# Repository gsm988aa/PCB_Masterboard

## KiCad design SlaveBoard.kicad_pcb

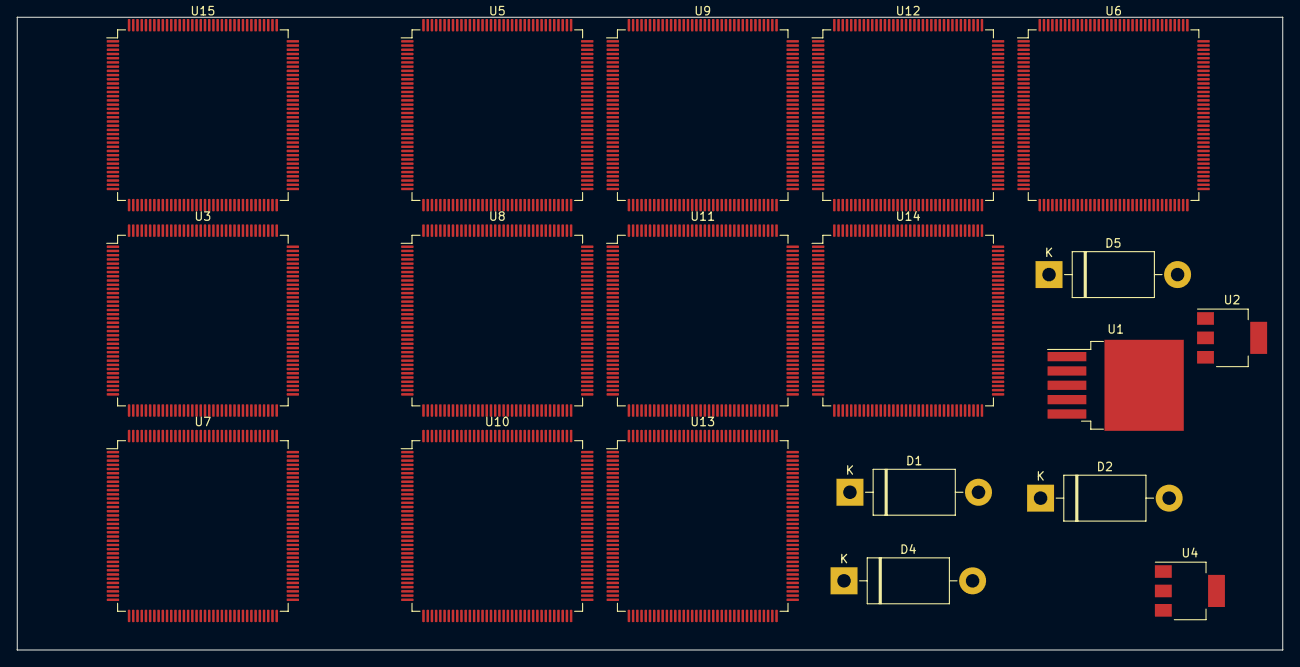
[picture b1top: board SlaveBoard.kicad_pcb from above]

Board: 2 copper layers, 150.0 x 75.0 mm, 19 parts (0 on the bottom side), 61 nets, no tracks yet.

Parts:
D1, D4: 1N5822; D_DO-201AD_P15.24mm_Horizontal
D2, D5: SMAJ5.0A; D_DO-201AD_P15.24mm_Horizontal
U1: LM2596S-5.0; TO-263-5_TabPin3
U2, U4: AMS1117-3.3; SOT-223-3_TabPin2
U3, U5, U6, U7, U8, U9, U10, U11, U12, U13, U14, U15: STM32F103ZETx; LQFP-144_20x20mm_P0.5mm

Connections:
+3V3: U2.2, U4.2
+5V: D2.1, D5.1, U1.2, U2.3, U4.3
GND: D2.2, D4.2, D5.2, U1.3, U1.5, U2.1, U4.1
M_SPI1_MISO: U5.42, U8.42, U9.42, U10.42, U11.42, U12.42, U13.42, U14.42, U15.42
M_SPI1_MOSI: U5.43, U8.43, U9.43, U10.43, U11.43, U12.43, U13.43, U14.43, U15.43
M_SPI1_SCK: U5.41, U8.41, U9.41, U10.41, U11.41, U12.41, U13.41, U14.41, U15.41
unnamed: D1.1, U1.1
unnamed: D4.1, U1.4
S2_ADC01: U3.34, U5.34, U8.34, U9.34, U10.34, U11.34, U12.34, U13.34, U14.34, U15.34
S2_ADC02: U3.35, U5.35, U8.35, U9.35, U10.35, U11.35, U12.35, U13.35, U14.35, U15.35
S2_ADC03: U3.36, U5.36, U8.36, U9.36, U10.36, U11.36, U12.36, U13.36, U14.36, U15.36
S2_ADC04: U3.37, U5.37, U8.37, U9.37, U10.37, U11.37, U12.37, U13.37, U14.37, U15.37
S2_ADC05: U3.40, U5.40, U8.40, U9.40, U10.40, U11.40, U12.40, U13.40, U14.40, U15.40
S2_ADC06: U3.46, U5.46, U8.46, U9.46, U10.46, U11.46, U12.46, U13.46, U14.46, U15.46
S2_ADC07: U3.47, U5.47, U8.47, U9.47, U10.47, U11.47, U12.47, U13.47, U14.47, U15.47
S2_ADC08: U3.26, U5.26, U8.26, U9.26, U10.26, U11.26, U12.26, U13.26, U14.26, U15.26
S2_ADC09: U3.27, U5.27, U8.27, U9.27, U10.27, U11.27, U12.27, U13.27, U14.27, U15.27
S2_ADC10: U3.28, U5.28, U8.28, U9.28, U10.28, U11.28, U12.28, U13.28, U14.28, U15.28
S2_ADC11: U3.29, U5.29, U8.29, U9.29, U10.29, U11.29, U12.29, U13.29, U14.29, U15.29
S2_ADC12: U3.44, U5.44, U8.44, U9.44, U10.44, U11.44, U12.44, U13.44, U14.44, U15.44
S2_ADC13: U3.45, U5.45, U8.45, U9.45, U10.45, U11.45, U12.45, U13.45, U14.45, U15.45
S2_ADC14: U3.18, U5.18, U8.18, U9.18, U10.18, U11.18, U12.18, U13.18, U14.18, U15.18
S2_ADC15: U3.19, U5.19, U8.19, U9.19, U10.19, U11.19, U12.19, U13.19, U14.19, U15.19
S2_ADC16: U3.20, U5.20, U8.20, U9.20, U10.20, U11.20, U12.20, U13.20, U14.20, U15.20
S2_ADC17: U3.21, U5.21, U8.21, U9.21, U10.21, U11.21, U12.21, U13.21, U14.21, U15.21
S2_ADC18: U3.22, U5.22, U8.22, U9.22, U10.22, U11.22, U12.22, U13.22, U14.22, U15.22
S2_S3_SPI2_MISO: U3.75, U5.75, U6.42, U8.75, U9.75, U10.75, U11.75, U12.75, U13.75, U14.75, U15.75
S2_S3_SPI2_MOSI: U3.76, U5.76, U6.43, U8.76, U9.76, U10.76, U11.76, U12.76, U13.76, U14.76, U15.76
S2_S3_SPI2_SCLK: U3.74, U5.74, U6.41, U8.74, U9.74, U10.74, U11.74, U12.74, U13.74, U14.74, U15.74
S2_S4_SPI3_MISO: U3.134, U5.134, U7.42, U8.134, U9.134, U10.134, U11.134, U12.134, U13.134, U14.134, U15.134
S2_S4_SPI3_MOSI: U3.135, U5.135, U7.43, U8.135, U9.135, U10.135, U11.135, U12.135, U13.135, U14.135, U15.135
S2_S4_SPI3_SCLK: U3.133, U5.133, U7.41, U8.133, U9.133, U10.133, U11.133, U12.133, U13.133, U14.133, U15.133
S2_SWCLK: U3.109, U5.109, U8.109, U9.109, U10.109, U11.109, U12.109, U13.109, U14.109, U15.109
S2_SWDIO: U3.105, U5.105, U8.105, U9.105, U10.105, U11.105, U12.105, U13.105, U14.105, U15.105
S2_VDD1: U3.17, U5.17, U8.17, U9.17, U10.17, U11.17, U12.17, U13.17, U14.17, U15.17
S2_VDD2: U3.39, U5.39, U8.39, U9.39, U10.39, U11.39, U12.39, U13.39, U14.39, U15.39
S2_VDD3: U3.52, U5.52, U8.52, U9.52, U10.52, U11.52, U12.52, U13.52, U14.52, U15.52
S2_VDD4: U3.62, U5.62, U8.62, U9.62, U10.62, U11.62, U12.62, U13.62, U14.62, U15.62
S2_VDD5: U3.72, U5.72, U8.72, U9.72, U10.72, U11.72, U12.72, U13.72, U14.72, U15.72
S2_VDD6: U3.84, U5.84, U8.84, U9.84, U10.84, U11.84, U12.84, U13.84, U14.84, U15.84
S2_VDD7: U3.95, U5.95, U8.95, U9.95, U10.95, U11.95, U12.95, U13.95, U14.95, U15.95
S2_VDD8: U3.108, U5.108, U8.108, U9.108, U10.108, U11.108, U12.108, U13.108, U14.108, U15.108
S2_VDD9: U3.121, U5.121, U8.121, U9.121, U10.121, U11.121, U12.121, U13.121, U14.121, U15.121
S2_VDD10: U3.131, U5.131, U8.131, U9.131, U10.131, U11.131, U12.131, U13.131, U14.131, U15.131
S2_VDD11: U3.144, U5.144, U8.144, U9.144, U10.144, U11.144, U12.144, U13.144, U14.144, U15.144
S2_VDDA: U3.33, U5.33, U8.33, U9.33, U10.33, U11.33, U12.33, U13.33, U14.33, U15.33
S2_VREF+: U3.32, U5.32, U8.32, U9.32, U10.32, U11.32, U12.32, U13.32, U14.32, U15.32
S2_VREF-: U3.31, U5.31, U8.31, U9.31, U10.31, U11.31, U12.31, U13.31, U14.31, U15.31
S2_VSS1: U3.16, U5.16, U8.16, U9.16, U10.16, U11.16, U12.16, U13.16, U14.16, U15.16
S2_VSS2: U3.38, U5.38, U8.38, U9.38, U10.38, U11.38, U12.38, U13.38, U14.38, U15.38
S2_VSS3: U3.51, U5.51, U8.51, U9.51, U10.51, U11.51, U12.51, U13.51, U14.51, U15.51
S2_VSS4: U3.61, U5.61, U8.61, U9.61, U10.61, U11.61, U12.61, U13.61, U14.61, U15.61
S2_VSS5: U3.71, U5.71, U8.71, U9.71, U10.71, U11.71, U12.71, U13.71, U14.71, U15.71
S2_VSS6: U3.83, U5.83, U8.83, U9.83, U10.83, U11.83, U12.83, U13.83, U14.83, U15.83
S2_VSS7: U3.94, U5.94, U8.94, U9.94, U10.94, U11.94, U12.94, U13.94, U14.94, U15.94
S2_VSS8: U3.107, U5.107, U8.107, U9.107, U10.107, U11.107, U12.107, U13.107, U14.107, U15.107
S2_VSS9: U3.120, U5.120, U8.120, U9.120, U10.120, U11.120, U12.120, U13.120, U14.120, U15.120
S2_VSS10: U3.130, U5.130, U8.130, U9.130, U10.130, U11.130, U12.130, U13.130, U14.130, U15.130
S2_VSS11: U3.143, U5.143, U8.143, U9.143, U10.143, U11.143, U12.143, U13.143, U14.143, U15.143
S2_VSSA: U3.30, U5.30, U8.30, U9.30, U10.30, U11.30, U12.30, U13.30, U14.30, U15.30
SW_RESET: U3.3, U5.3, U6.3, U7.3, U8.3, U9.3, U10.3, U11.3, U12.3, U13.3, U14.3, U15.3

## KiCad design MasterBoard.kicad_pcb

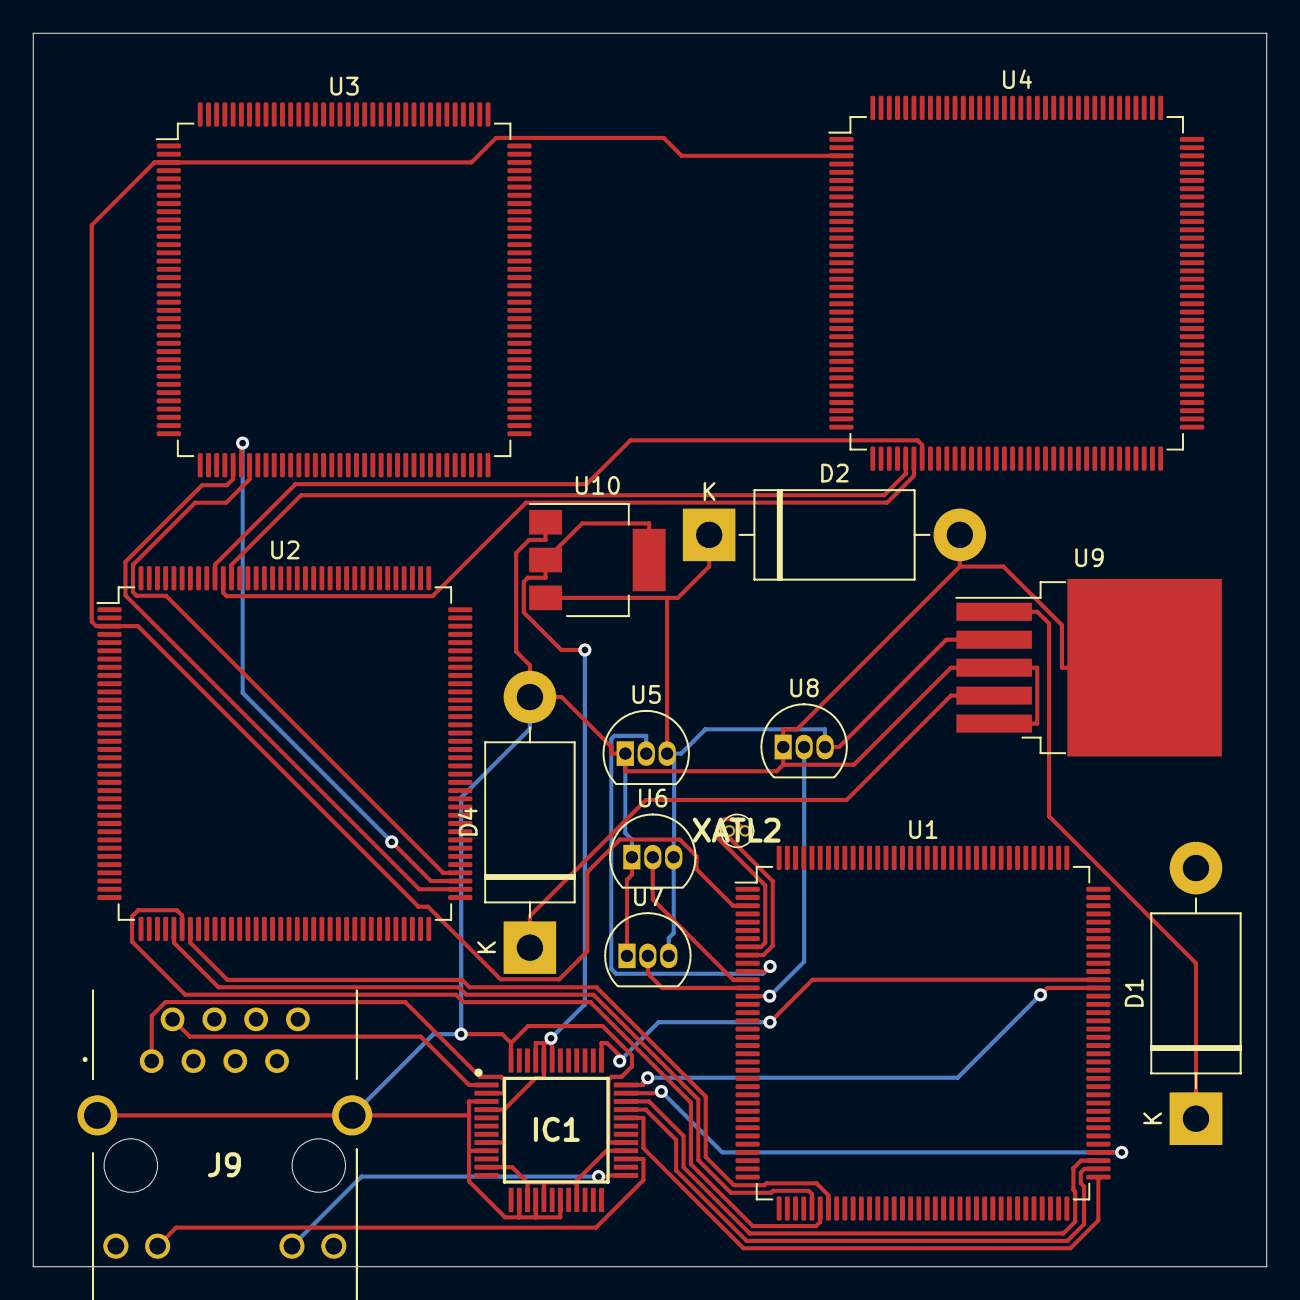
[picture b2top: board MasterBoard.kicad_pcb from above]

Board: 2 copper layers, 75.0 x 75.0 mm, 16 parts (0 on the bottom side), 31 nets.

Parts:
D1, D4: 1N5822; D_DO-201AD_P15.24mm_Horizontal
D2: SMAJ5.0A; D_DO-201AD_P15.24mm_Horizontal
IC1: W5500; QFP50P900X900X160-48N
J9: HR911105A
U1, U2, U3, U4: STM32F103ZETx; LQFP-144_20x20mm_P0.5mm
U5, U6, U7, U8: DS18B20; TO-92_Inline
U9: LM2596S-5.0; TO-263-5_TabPin3
U10: AMS1117-3.3; SOT-223-3_TabPin2
XATL2: 32.768kHz; CFS20632768DZFB

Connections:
+3V3: IC1.4, IC1.8, IC1.11, IC1.15, IC1.17, IC1.21, IC1.28, IC1.43, IC1.44, IC1.45, U10.2
+5V: D2.1, U5.3, U6.3, U7.3, U8.3, U9.2, U10.3
ACTLED: IC1.27, J9.10
DQ1: U1.11, U5.2
DQ2: U1.12, U6.2
DQ3: U1.13, U7.2
DQ4: U1.14, U8.2
GND: D2.2, D4.2, IC1.3, IC1.9, IC1.14, IC1.16, IC1.19, IC1.29, IC1.48, J9.MH1, J9.MH2, U5.1, U6.1, U7.1, U8.1, U9.3, U9.5, U10.1
LINKLED: IC1.25, J9.11
M_SPI1_MISO: U1.42, U2.42
M_SPI1_MOSI: U1.43, U2.43
M_SPI1_SCK: U1.41, U2.41
unnamed: D1.1, U9.1
unnamed: D4.1, U9.4
OSC32_IN: U1.8, XATL2.2
OSC32_OUT: U1.9, XATL2.1
S2_S3_SPI2_MISO: U2.75, U3.42
S2_S3_SPI2_MOSI: U2.76, U3.43
S2_S3_SPI2_SCLK: U2.74, U3.41
S2_S4_SPI3_MISO: U2.134, U4.42
S2_S4_SPI3_MOSI: U2.135, U4.43
S2_S4_SPI3_SCLK: U2.133, U4.41
SW_RESET: U1.3, U2.3, U3.3, U4.3
TXN: IC1.1, J9.2
TXP: IC1.2, J9.1
W5500_INT: IC1.36, U1.96
W5500_RST: IC1.37, U1.97
W5500_SCS: IC1.32, U1.73
W5500_SPI2_MISO: IC1.34, U1.75
W5500_SPI2_MOSI: IC1.35, U1.76
W5500_SPI2_SCLK: IC1.33, U1.74

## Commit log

2020-12-15 kicad final
